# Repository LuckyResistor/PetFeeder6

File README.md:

# Files for the Pet-Feeder 6 Project

## Details

You will find all details of this project here:

https://luckyresistor.me/projects/lets-print-a-cat-pet-feeding-device/

## License

https://creativecommons.org/licenses/by-sa/4.0/

<br />This work is licensed under a <a rel="license" href="http://creativecommons.org/licenses/by/4.0/">Creative Commons Attribution 4.0 International License</a>.

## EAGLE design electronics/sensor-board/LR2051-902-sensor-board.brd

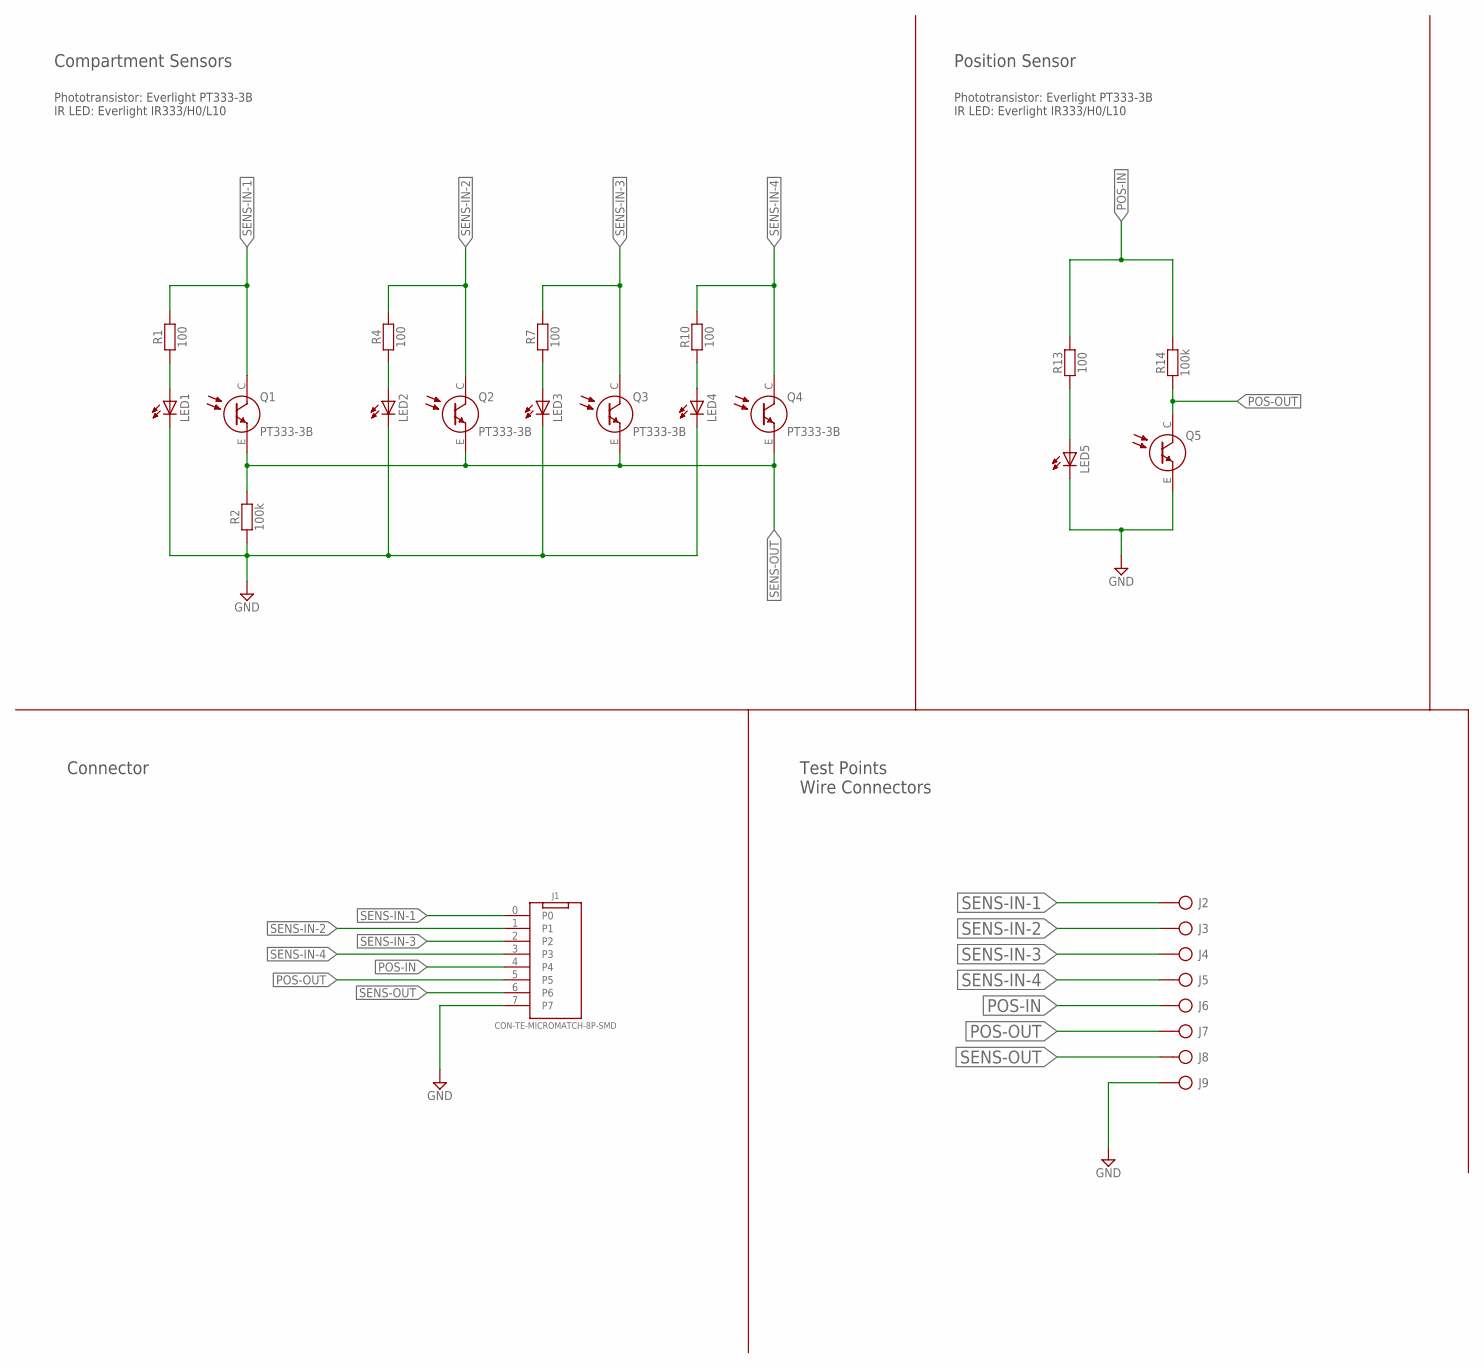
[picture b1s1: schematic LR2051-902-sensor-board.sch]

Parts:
J1: CON-TE-MICROMATCH-8P-SMD; CON-TE-MICROMATCH-2178711-8
J2, J3, J4, J5, J6, J7, J8, J9: CON-HOLE-D0.9
LED1, LED2, LED3, LED4, LED5: LED5MM
Q1, Q2, Q3, Q4: PT333-3B; Q-PHOTO-2P-TH-5MM
Q5: Q-PHOTO-TH-5MM; Q-PHOTO-2P-TH-5MM
R1, R4, R7, R10, R13: 100; R-0805-HANDSOLDER
R2, R14: 100k; R-0805-HANDSOLDER

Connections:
GND: J1.7, J9.1, LED1.K (C), LED2.K (C), LED3.K (C), LED4.K (C), LED5.K (C), Q5.E, R2.1
unnamed: LED1.A, R1.1
unnamed: LED2.A, R4.1
unnamed: LED3.A, R7.1
unnamed: LED4.A, R10.1
unnamed: LED5.A, R13.1
POS-IN: J1.4, J6.1, R13.2, R14.2
POS-OUT: J1.5, J7.1, Q5.C, R14.1
SENS-IN-1: J1.0, J2.1, Q1.C, R1.2
SENS-IN-2: J1.1, J3.1, Q2.C, R4.2
SENS-IN-3: J1.2, J4.1, Q3.C, R7.2
SENS-IN-4: J1.3, J5.1, Q4.C, R10.2
SENS-OUT: J1.6, J8.1, Q1.E, Q2.E, Q3.E, Q4.E, R2.2

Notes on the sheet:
Compartment Sensors
Position Sensor
Connector
Test Points Wire Connectors
Phototransistor: Everlight PT333-3B IR LED: Everlight IR333/H0/L10

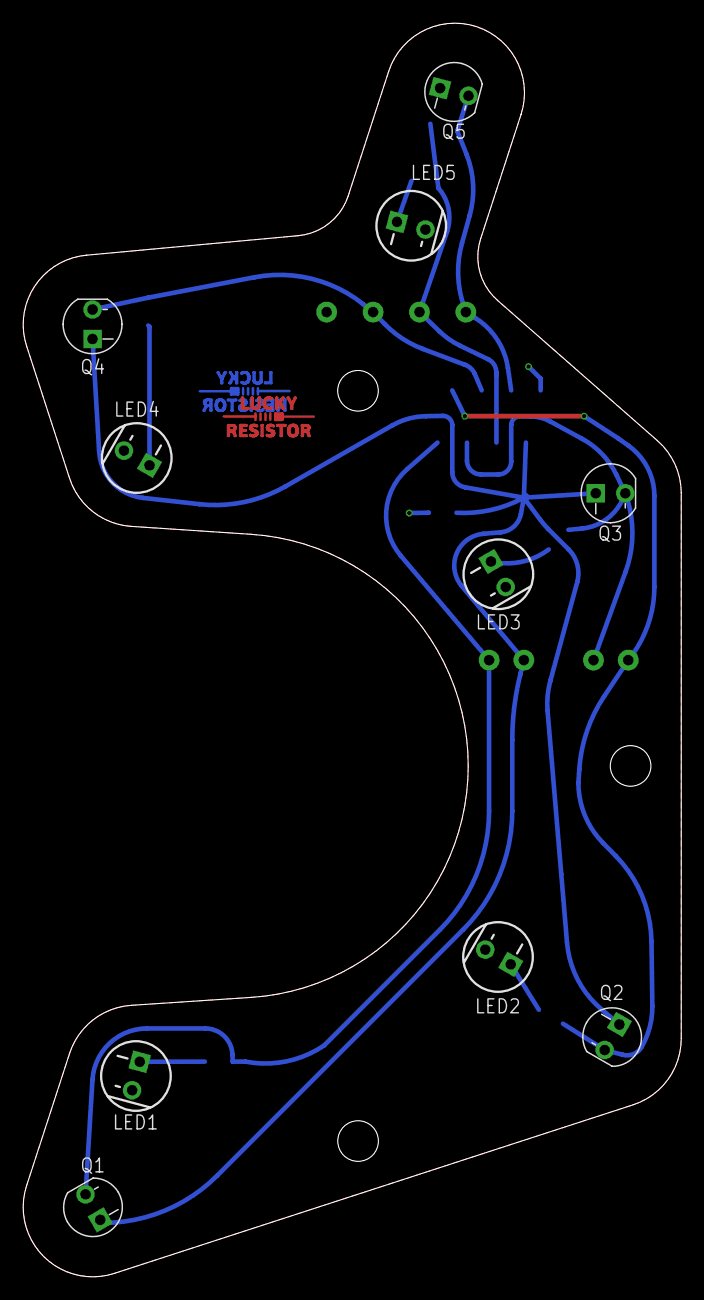
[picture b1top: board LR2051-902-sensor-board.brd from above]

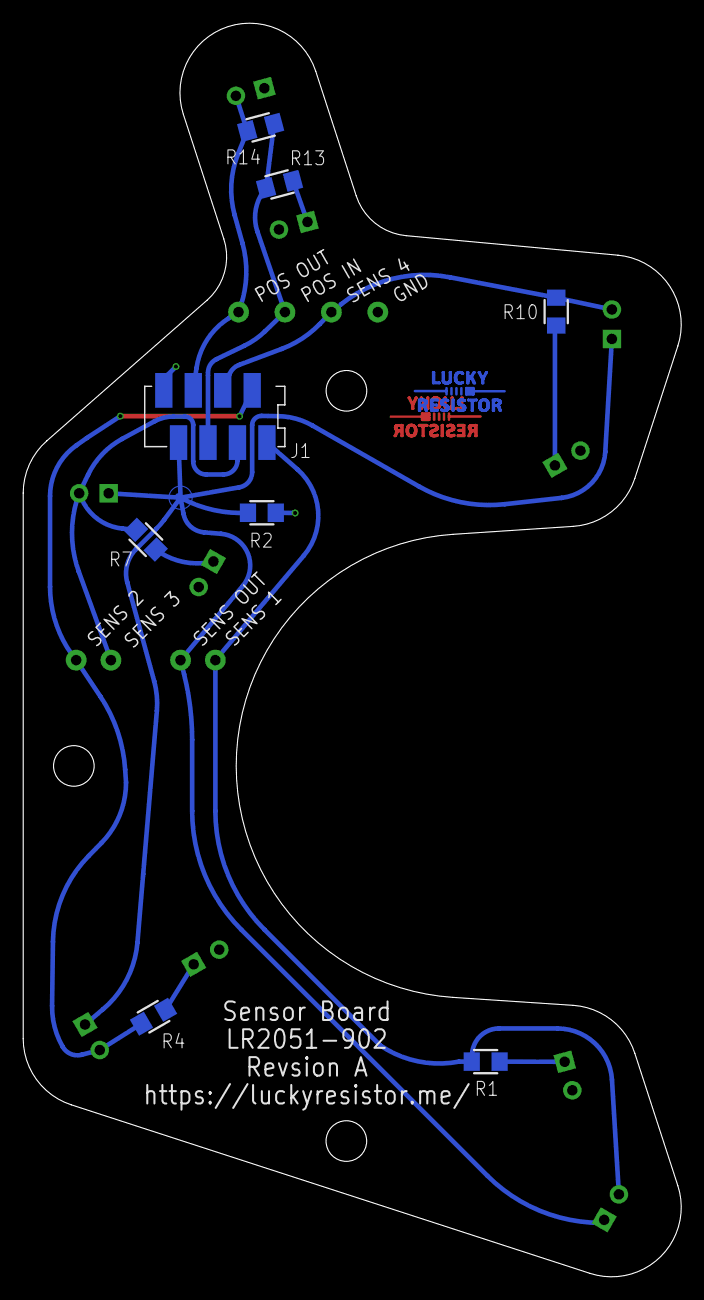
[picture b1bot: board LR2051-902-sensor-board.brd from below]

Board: 2 copper layers, 56.7 x 108.1 mm, 28 parts (17 on the bottom side), 13 nets.

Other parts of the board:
U$1, U$2: LR_LOGO_COPPER_8MM_NOMASK

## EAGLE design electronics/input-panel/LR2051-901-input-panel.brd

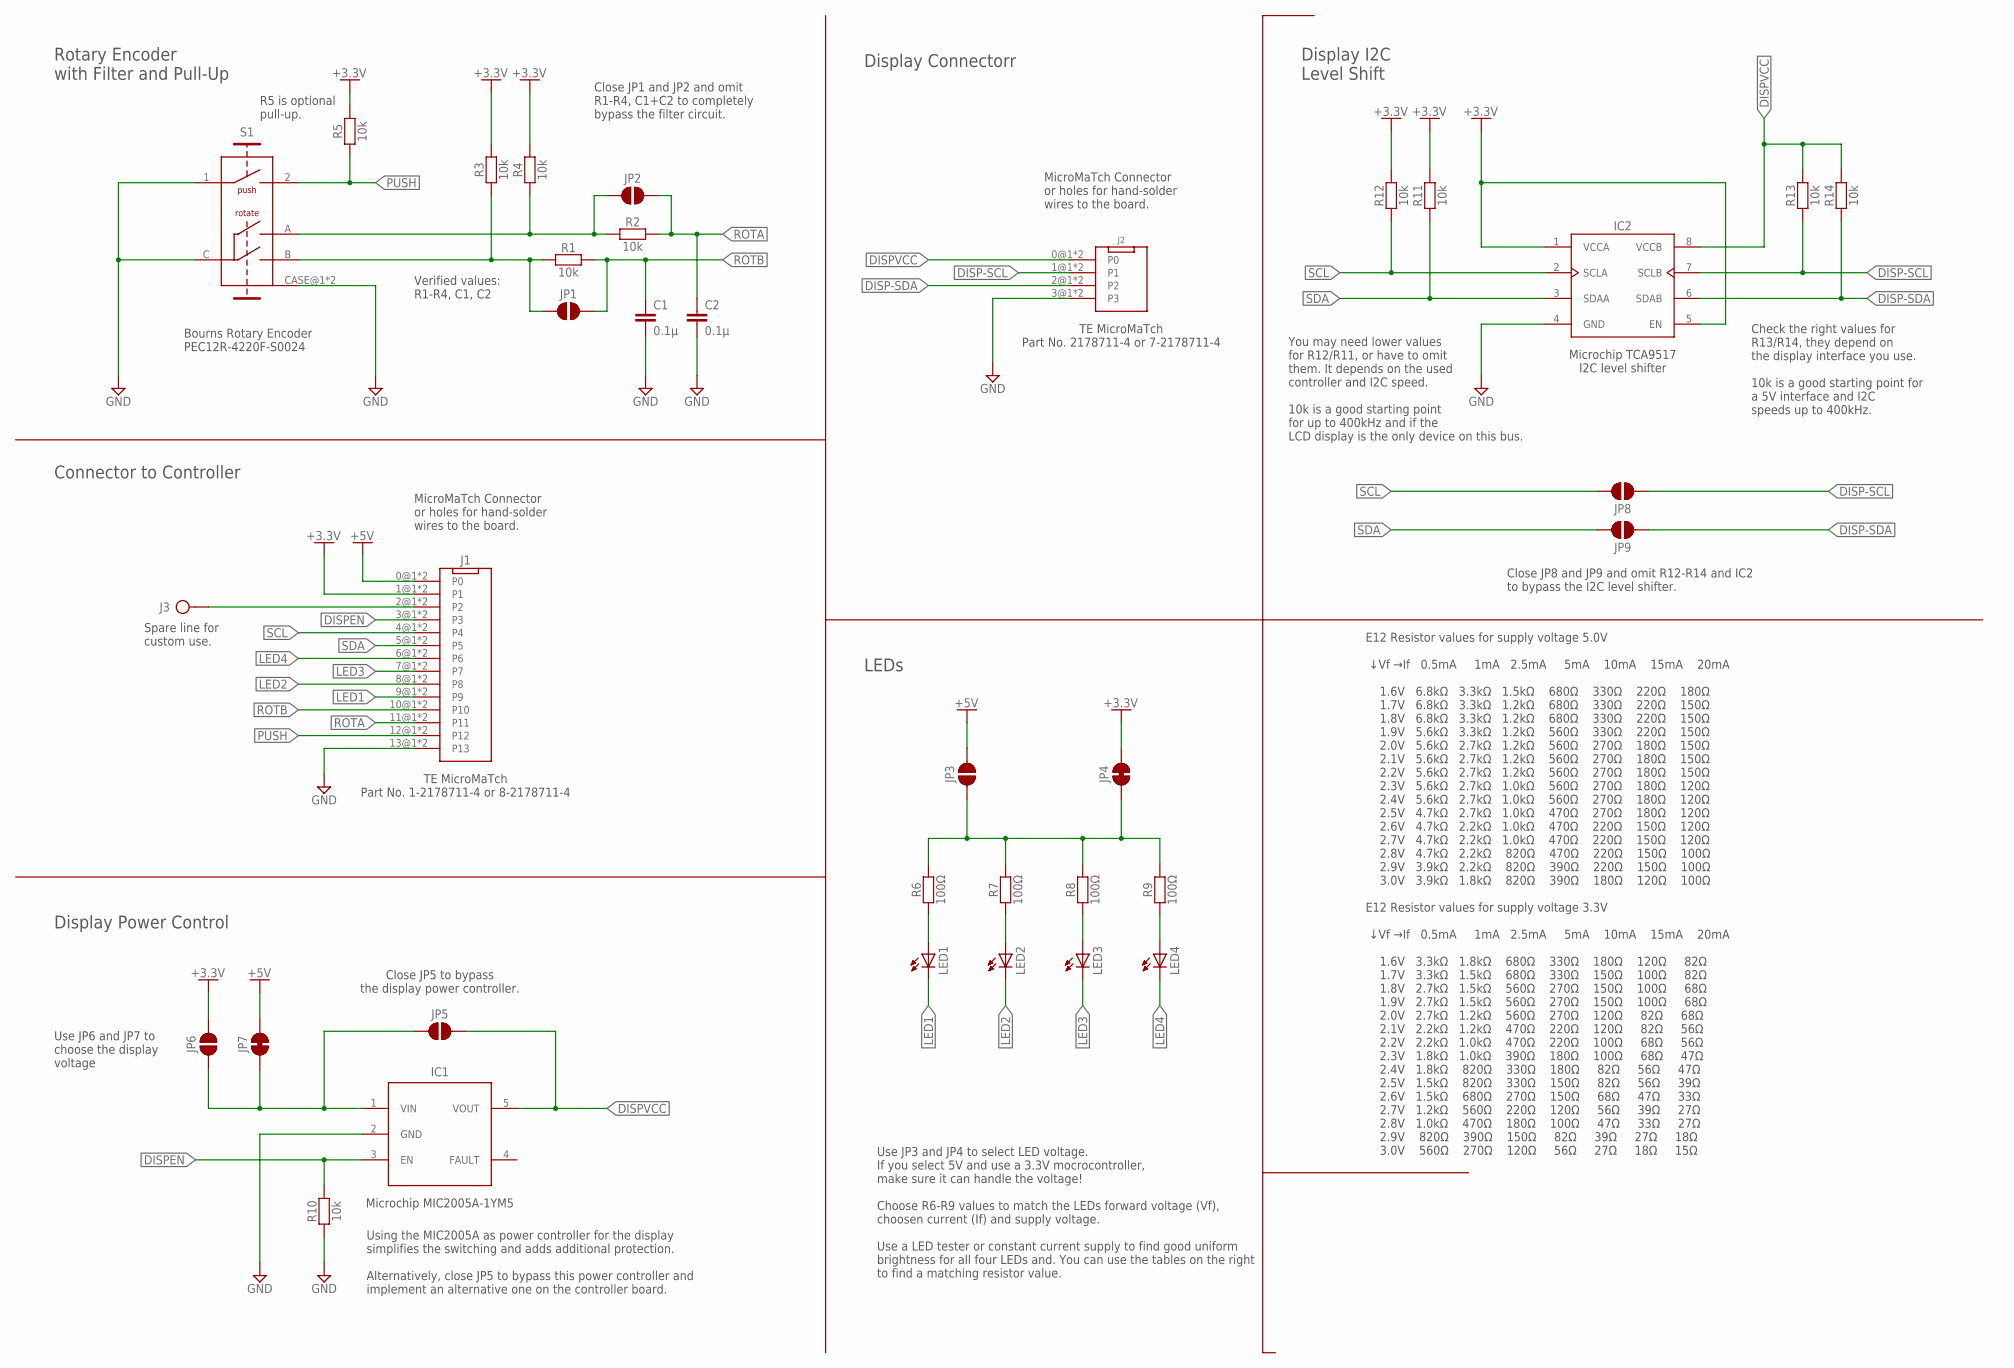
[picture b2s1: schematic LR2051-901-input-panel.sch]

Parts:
C1, C2: 0.1µ; CAPACITOR-0805-VISHAY
IC1: IC-MIC2005A-1YM5; SOT23-5
IC2: IC-TCA9517; SOIC127P599X175-8N
J1: CON-TE-MICROMATCH-14P-SMD+TH; CON-TE-MICROMATCH-1-2178711-4+TH
J2: CON-TE-MICROMATCH-4P-SMD+TH; CON-TE-MICROMATCH-2178711-4+TH
J3: CON-HOLE-D0.9
JP1, JP2, JP3, JP5, JP6, JP8, JP9: J-SMD-OFF
JP4, JP7: J-SMD-ON
LED1, LED2, LED3, LED4: LED5MM
R1, R2, R3, R4, R5, R10, R11, R12, R13, R14: 10k; R-0805-HANDSOLDER
R6, R7, R8, R9: 100Ω; R-0805-HANDSOLDER
S1: ENC-BOURNS-PEC12R-4220F-S0024

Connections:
+3.3V: IC2.1 (VCCA), IC2.5 (EN), J1.1@1 (P1), J1.1@2 (P1), JP4.2, JP6.2, R3.2, R4.2, R5.2, R11.2, R12.2
+5V: J1.0@1 (P0), J1.0@2 (P0), JP3.2, JP7.2
DISP-SCL: IC2.7 (SCLB), J2.1@1 (P1), J2.1@2 (P1), JP8.1, R13.1
DISP-SDA: IC2.6 (SDAB), J2.2@1 (P2), J2.2@2 (P2), JP9.1, R14.1
DISP-VIN: IC1.1 (VIN), JP5.1, JP6.1, JP7.1
DISPEN: IC1.3 (EN), J1.3@1 (P3), J1.3@2 (P3), R10.2
DISPVCC: IC1.5 (VOUT), IC2.8 (VCCB), J2.0@1 (P0), J2.0@2 (P0), JP5.2, R13.2, R14.2
GND: C1.2, C2.2, IC1.2 (GND), IC2.4 (GND), J1.13@1 (P13), J1.13@2 (P13), J2.3@1 (P3), J2.3@2 (P3), R10.1, S1.1 (S), S1.C, S1.CASE@1 (GND), S1.CASE@2 (GND)
LED1: J1.9@1 (P9), J1.9@2 (P9), LED1.K (C)
LED2: J1.8@1 (P8), J1.8@2 (P8), LED2.K (C)
LED3: J1.7@1 (P7), J1.7@2 (P7), LED3.K (C)
LED4: J1.6@1 (P6), J1.6@2 (P6), LED4.K (C)
LED-VCC: JP3.1, JP4.1, R6.2, R7.2, R8.2, R9.2
unnamed: JP1.1, R1.1, R3.1, S1.B
unnamed: J1.2@1 (P2), J1.2@2 (P2), J3.1
unnamed: JP2.1, R2.1, R4.1, S1.A
unnamed: LED1.A, R6.1
unnamed: LED2.A, R7.1
unnamed: LED3.A, R8.1
unnamed: LED4.A, R9.1
PUSH: J1.12@1 (P12), J1.12@2 (P12), R5.1, S1.2 (S)
ROTA: C2.1, J1.11@1 (P11), J1.11@2 (P11), JP2.2, R2.2
ROTB: C1.1, J1.10@1 (P10), J1.10@2 (P10), JP1.2, R1.2
SCL: IC2.2 (SCLA), J1.4@1 (P4), J1.4@2 (P4), JP8.2, R12.1
SDA: IC2.3 (SDAA), J1.5@1 (P5), J1.5@2 (P5), JP9.2, R11.1

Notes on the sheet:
Rotary Encoder with Filter and Pull-Up
Connector to Controller
LEDs
Display Power Control
Display I2C Level Shift
Display Connectorr
MicroMaTch Connector or holes for hand-solder wires to the board.
Spare line for custom use.
Close JP1 and JP2 and omit R1-R4, C1+C2 to completely bypass the filter circuit.
R5 is optional pull-up.
Bourns Rotary Encoder PEC12R-4220F-S0024
Use JP3 and JP4 to select LED voltage. If you select 5V and use a 3.3V mocrocontroller, make sure it can handle the voltage\! Choose R6-R9 values to match the LEDs forward voltage (Vf), choosen current (If) and supply voltage. Use a LED tester or constant current supply to find good uniform brightn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
Microchip TCA9517 I2C level shifter
You may need lower values for R12/R11, or have to omit them. It depends on the used controller and I2C speed. 10k is a good starting point for up to 400kHz and if the LCD display is the only device on this bus.
Check the right values for R13/R14, they depend on the display interface you use. 10k is a good starting point for a 5V interface and I2C speeds up to 400kHz.
Close JP8 and JP9 and omit R12-R14 and IC2 to bypass the I2C level shifter.
TE MicroMaTch Part No. 1-2178711-4 or 8-2178711-4
TE MicroMaTch Part No. 2178711-4 or 7-2178711-4
Use JP6 and JP7 to choose the display voltage
Close JP5 to bypass the display power controller.
Microchip MIC2005A-1YM5
Using the MIC2005A as power controller for the display simplifies the switching and adds additional protection. Alternatively, close JP5 to bypass this power controller and implement an alternative one on the controller board.
Verified values: R1-R4, C1, C2
E12 Resistor values for supply voltage 3.3V ↓Vf →If 0.5mA 1mA 2.5mA 5mA 10mA 15mA 20mA 1.6V 3.3kΩ 1.8kΩ 680Ω 330Ω 180Ω 120Ω 82Ω 1.7V 3.3kΩ 1.5kΩ 680Ω 330Ω 150Ω 100Ω 82Ω 1.8V 2.7kΩ 1.5kΩ 560Ω 270Ω 150Ω 100Ω 68Ω 1.9V 2.7kΩ 1.5kΩ 560Ω 270Ω 150Ω 100Ω 68Ω 2.0V 2.7kΩ 1.2kΩ 560Ω 270Ω 120Ω 82Ω 68Ω 2.1V 2.2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
E12 Resistor values for supply voltage 5.0V ↓Vf →If 0.5mA 1mA 2.5mA 5mA 10mA 15mA 20mA 1.6V 6.8kΩ 3.3kΩ 1.5kΩ 680Ω 330Ω 220Ω 180Ω 1.7V 6.8kΩ 3.3kΩ 1.2kΩ 680Ω 330Ω 220Ω 150Ω 1.8V 6.8kΩ 3.3kΩ 1.2kΩ 680Ω 330Ω 220Ω 150Ω 1.9V 5.6kΩ 3.3kΩ 1.2kΩ 560Ω 330Ω 220Ω 150Ω 2.0V 5.6kΩ 2.7kΩ 1.2kΩ 560Ω 270Ω 180Ω 15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

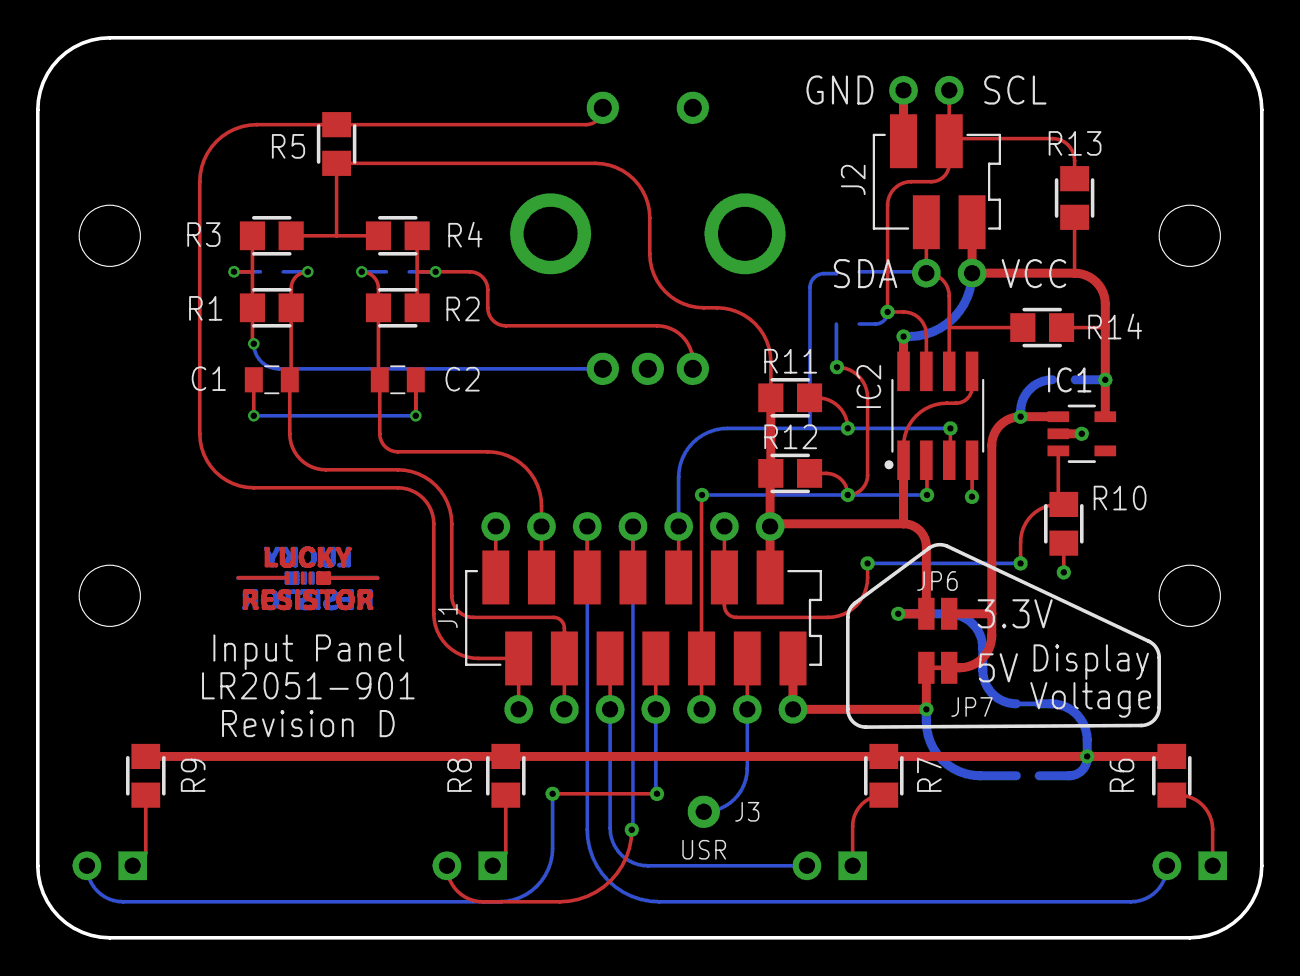
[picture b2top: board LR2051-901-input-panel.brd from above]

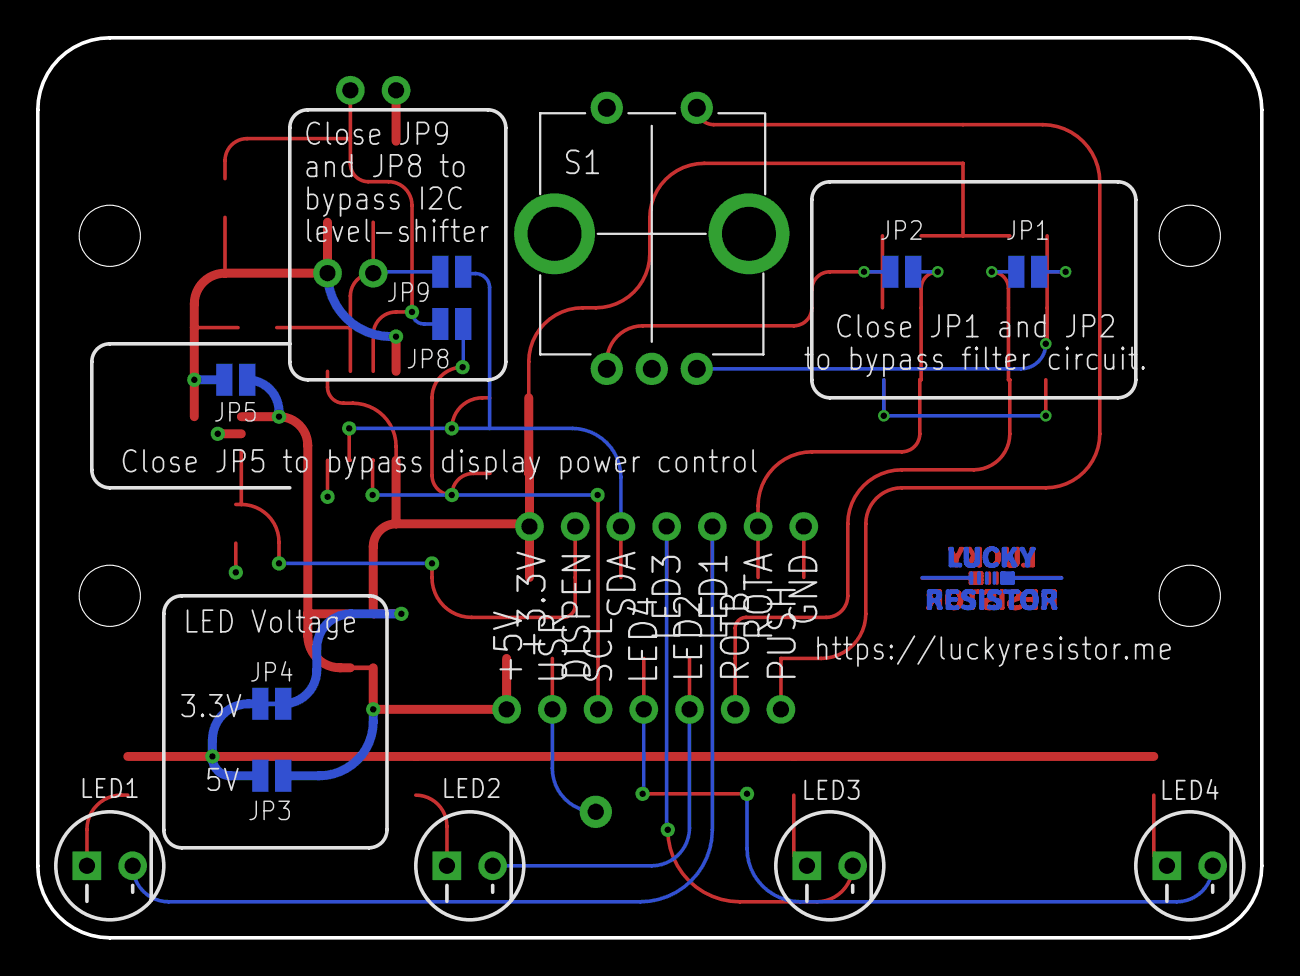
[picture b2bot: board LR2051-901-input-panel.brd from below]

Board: 2 copper layers, 68.0 x 50.0 mm, 37 parts (13 on the bottom side), 25 nets.

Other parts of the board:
U$1, U$2: LR_LOGO_COPPER_8MM_NOMASK

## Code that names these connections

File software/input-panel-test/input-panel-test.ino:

//
// Pet Feeder Input Panel Demo
// ====================================================================================
// Copyright (c)2021 by Lucky Resistor. https://luckyresistor.me/
//


#include <Arduino.h>
#include <Wire.h>
#include <Adafruit_LiquidCrystal.h>

#include <cstdint>


// Create an instance of the LCD driver.
Adafruit_LiquidCrystal lcd(0);

// Input events
enum class Input : uint8_t {
  None = 0, // No input 
  Push, // Push button pressed.
  Left, // Rotated left
  Right // Rotated right
};


// The connections from the input panel to the pins of the MCU.
//
const uint8_t statusLed = 13;
const uint8_t led1 = 5;
const uint8_t led2 = 6;
const uint8_t led3 = 10;
const uint8_t led4 = 11;
const uint8_t displayEnable = 12;
const uint8_t buttonPush = 9;
const uint8_t buttonRotB = 0;
const uint8_t buttonRotA = 1;

// Array to address the LEDs via index
const uint8_t leds[] = {led1, led2, led3, led4};

// Working set:

// The last state of the rotary encoder.
uint8_t lastRotaryState = 0;
// The sequence of the last rotary states.
uint8_t lastRotaryStates[4];
// The last state of the push button.
bool lastPushButtonState = false;
// The time when the push button was pressed.
uint32_t pushButtonPressedTime = 0;

// The maximum number of input events.
const uint8_t inputMaximum = 32;
// An array with the last 32 input events.
Input inputs[inputMaximum];
// The current number of input events.
volatile uint8_t inputCount = 0;

// Counter for the demo.
uint32_t counter = 0;

// Enable the LED at the given index.
//
void setLedEnabled(uint8_t ledIndex, bool enabled) {
  const auto pin = leds[ledIndex];
  if (enabled) {
    digitalWrite(pin, LOW);
    pinMode(pin, OUTPUT);
  } else {
    digitalWrite(pin, LOW);
    pinMode(pin, INPUT);
  }
}


// Push an input event in the queue.
//
void pushInput(Input input)
{
  if (inputCount < inputMaximum) {
    inputs[inputCount] = input;
    inputCount += 1;
  }
}

// Check for inputs.
//
Input getInput()
{
  noInterrupts();
  Input result = Input::None;
  if (inputCount > 0) {
    result = inputs[0];
    memmove(inputs, inputs+1, inputMaximum-1);
    inputCount -= 1;
  }
  interrupts();
  return result;
}


// Get the current state of the rotary encoder.
//
uint8_t getRotaryState()
{
  const bool rotA = (digitalRead(buttonRotA) == LOW);
  const bool rotB = (digitalRead(buttonRotB) == LOW);
  return (rotA ? 0b01 : 0b00) | (rotB ? 0b10 : 0b00);
}


// Get the current state of the push button.
//
uint8_t getPushButtonState()
{
  return (digitalRead(buttonPush) == LOW);
}


// Process the button states everytime the signal changes on one of the inputs.
//
void processButtons()
{
  const uint8_t rotaryState = getRotaryState();
  if (lastRotaryState != rotaryState) {
    lastRotaryState = rotaryState;
    // It has moved. Push this state into the array
    lastRotaryStates[3] = lastRotaryStates[2];
    lastRotaryStates[2] = lastRotaryStates[1];
    lastRotaryStates[1] = lastRotaryStates[0];
    lastRotaryStates[0] = rotaryState;
    // If we reached the zero state, check if we made a proper rotation.
    if (rotaryState == 0b00) {
      if (lastRotaryStates[1] == 0b10 && lastRotaryStates[2] == 0b11 && lastRotaryStates[3] == 0b01) {
        pushInput(Input::Left);
      } else if (lastRotaryStates[1] == 0b01 && lastRotaryStates[2] == 0b11 && lastRotaryStates[3] == 0b10) {
        pushInput(Input::Right);
      }
    }

    // display the rotary input
    setLedEnabled(1, (rotaryState & 0b01) != 0);
    setLedEnabled(2, (rotaryState & 0b10) != 0);
  }

  const bool pushButtonState = getPushButtonState();
  if (pushButtonState != lastPushButtonState) {
    lastPushButtonState = pushButtonState;
    if (pushButtonState) {
      // pushed, note the time.
      pushButtonPressedTime = millis();
    } else {
      // released
      const int32_t duration = static_cast<int32_t>(millis() - pushButtonPressedTime);
      if (duration > 50 && duration < 2000) {
        // valid button press.
        pushInput(Input::Push);
      }
    }
    // display button input.
    setLedEnabled(3, pushButtonState);
  }
}


void setup() {
  
  // Setup hardware
  pinMode(statusLed, OUTPUT);
  digitalWrite(statusLed, LOW);
  pinMode(displayEnable, OUTPUT);
  digitalWrite(displayEnable, LOW);
  pinMode(buttonPush, INPUT);
  pinMode(buttonRotB, INPUT);
  pinMode(buttonRotA, INPUT);

  // Initialize the rotary state.
  lastRotaryState = getRotaryState();

  // Attach button interrupts
  attachInterrupt(digitalPinToInterrupt(buttonPush), processButtons, CHANGE);
  attachInterrupt(digitalPinToInterrupt(buttonRotB), processButtons, CHANGE);
  attachInterrupt(digitalPinToInterrupt(buttonRotA), processButtons, CHANGE);

  // Test all LEDs
  for (uint8_t i = 0; i < 4; ++i) {
    for (uint8_t j = 0; j < 4; ++j) {
      setLedEnabled(j, true);
      delay(50);
      setLedEnabled(j, false);
    }
  }

  // Enable the display.
  digitalWrite(displayEnable, HIGH);
  delay(500); // wait until the chip is ready.
  // Initialize the display library.
  lcd.begin(20, 4);
  // Increase the speed on the I2C bus.
  Wire.setClock(400000);
  // Enable the backlight.
  lcd.setBacklight(HIGH);

  // Write a welcome message.
  lcd.setCursor(3, 0);
  lcd.print("Lucky Resistor");
  lcd.setCursor(2, 1);
  lcd.print("Pet Feeder Demo");

  // Enable the green light
  setLedEnabled(0, true);

  // Set the position and enable a blinking cursor.
  lcd.setCursor(0, 3);
  lcd.cursor();
  lcd.blink();
}


void updateCounter(uint32_t value) 
{
  lcd.setCursor(0, 2);
  lcd.print(value);
  lcd.print("          ");
}


void writeInputEvent(char c)
{
  static uint8_t pos = 0;
  lcd.setCursor(pos, 3); 
  lcd.print(c);
  pos += 1;
  if (pos >= 20) {
    pos = 0;     
  }
  lcd.setCursor(pos, 3); 
}


void processInputs()
{
  auto input = getInput();
  while (input != Input::None) {
    if (input == Input::Push) {
      counter = 0;
      updateCounter(counter);
      writeInputEvent('P');
    } else if (input == Input::Left) {
      counter -= 1;
      updateCounter(counter);
      writeInputEvent('L');
    } else if (input == Input::Right) {
      counter += 1;
      updateCounter(counter);
      writeInputEvent('R');
    }
    input = getInput();
  }
}


void loop() {
  processInputs();
  delay(1);
}

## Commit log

2021-01-02 add all files for part 1
2021-01-02 add bearing mockups
2021-01-12 Preparing the files for the next part
2021-01-24 Adding the files for part 4.
2021-01-24 Add the LED cover.
2021-01-30 Adding the files for part 5.
2021-02-18 Adding the files for the 6. part of the series.
2021-04-03 File updates for part 7 of the series.
2021-04-05 Adding new file revisions for the turntable platform.
